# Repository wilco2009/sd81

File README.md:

# SD81 Booster — SD, sound, voice and memory interface for ZX81

An open hardware, open source project packing many features in a single interface.

## Credits

```
Hardware design & MCU firmware:  Alejandro Valero (wilco2009)
Z80 code / Modified ROM:         Pedro Gimeno (pgimeno)

Based on ZX81 ROM disassembly by Geoff Wearmouth
Preserved by Tomaž Šolc (https://www.tablix.org/~avian/spectrum/rom/)
```

## Features

- Load and save programs from/to a FAT32 microSD card in `.P` format, supporting common file and directory operations: list directory, copy/move/rename/delete files, change/create/remove directories.
- Up to 512 KB RAM, using a memory mapper in 8 KB blocks. There's also a simplified mode that allows up to 256 KB RAM, needing very simple paging code.
- The selected mapper page for any given block can be read back.
- Up to 128 user-defined characters. Compatible with the QuickSilva character definition mode — no longer restricted to the ROM's 64 characters and their inverses.
- AY-3-8910/12 sound chip emulation with `PLAY` command.
- AY VGM player, plays in background (does not support VGMs containing other chips than the AY).
- AY sound effects in background, via a programmable virtual machine (PEG).
- Speech synthesis based on the SP0256 chip (General Instrument), the same synthesiser used by the Currah MicroSpeech (ZX Spectrum) and The Voice (Videopac G7000/Odyssey 2). The `LOAD *SAY` command accepts English text directly.
- WAV audio file playback (uncompressed PCM).
- RGB colour video output, compatible with the Chroma81 interface standard.
- Real-time clock (RTC) with CR2032 backup battery.
- Programmable DB9 joystick port.
- Possibility to run code in the region between 32K and 48K (MC45 mode — see below).
- Minimal changes to the standard ROM. In particular, the ZX Printer and tape routines are preserved intact.

### What it doesn't do

- File names are restricted to characters supported by the ZX81 keyboard. The permitted characters for filenames are `A`–`Z`, `0`–`9`, `.`, `,`, `;`, `$`, `(`, `)`, `=`, `+`, `-`. The `/` character is the directory separator. Letters are treated as upper case when saving.
- AY sound chip emulation is not cycle-accurate.
- AY sound chip register access is not compatible with other interfaces.
- The memory mapping I/O port and layout are not compatible with other interfaces.
- There are no new BASIC keywords; most new functions are implemented through extensions to the `LOAD` and `SAVE` commands.

### Possible compatibility issues

- The SD81 Booster incorporates the functionality of the Chroma81 (RGB colour video) and QuickSilva (128 user-defined characters) interfaces. It is not designed to be used simultaneously with those physical interfaces connected at the same time.
- The memory area between 8 KB and 16 KB is no longer a mirror of the area between 0 and 8 KB.
- The same area is now read/write rather than read-only. If a program writes to used areas within that space, the expanded commands may crash and a hardware reset will be necessary.
- The ROM changes 8 bytes with respect to the original. Programs that depend on those specific bytes may fail (considered highly unlikely in practice).
- The memory mapper I/O port may clash with that of other interfaces.
- The general command interface I/O ports might clash with those of other interfaces.
- The USB-C port uses a CH340G chip for serial console output (115200-8N1). In Spectrum mode, port FBh is used, which is incompatible with the ZX Printer.

## MC45

MC45 (Machine Code in blocks 4 and 5) is a mode that allows any Z80 instruction — not just those with opcodes in the ranges 40h–7Fh and C0h–FFh — to run in the address range 8000h–BFFFh. The drawback is that the display file can no longer be in that area, so BASIC programs larger than 16 KB cannot be loaded or written while this mode is active.

The interface already includes a 33Ω protective resistor on the M1 line internally. No modification to the ZX81 is required. There is no jumper to disable this feature on the current hardware version.

> **Note:** Some older documentation refers to a 680Ω resistor — that value applies to an alternative ZX81 hardware modification, not to the SD81 Booster itself.

## Getting started

The **SYS** folder must be present in the root of the microSD card — without it the interface will not start. It contains the ROM files required for operation.

See [MANUAL/ES/SD81_Manual_ES.md](MANUAL/ES/SD81_Manual_ES.md) for the full user manual in Spanish.

For the technical reference and MCU command descriptions, see the [DOC folder](DOC/).

## Firmware update

**Normal update (via SD bootloader):**
1. Copy the firmware `.bin` file (renamed as `firmware.bin`) to the root of the SD card.
2. Power on the ZX81. The bootloader detects the file, flashes it at `0x0800C000`, deletes it, and boots the application.

**Emergency recovery (via USB, for advanced users):**
1. Open the interface case and bridge the two upper pins of jumper **JP7** (on the component side, next to the USB-C port).
2. Connect the USB-C cable to a PC.
3. Use **STM32CubeProgrammer** to flash:
   - Bootloader at `0x08000000`
   - Application at `0x0800C000`

See [FIRMWARE/README_update.md](FIRMWARE/README_update.md) for detailed instructions.

## Building the ZX81 ROM

The ROM listing used here is the disassembly work of [Geoff Wearmouth](http://web.archive.org/web/20150815035607/http://www.wearmouth.demon.co.uk/zx81.htm), preserved by [Tomaž Šolc](https://www.tablix.org/~avian/spectrum/rom/).

The ROM can be built using [GNU binutils for Z80](https://github.com/atsidaev/binutils-z80), [Pasmo](https://pasmo.speccy.org/) or [MDL](https://github.com/santiontanon/mdlz80optimizer).

To build with GNU binutils:

    z80-unknown-coff-as sdmodrom.asm -o sdmodrom.o
    z80-unknown-coff-ld -Ttext 0 sdmodrom.o -o sdmodrom.bin

To build with Pasmo:

    pasmo sdmodrom.asm sdmodrom.bin

To build with MDL (dialects `pasmo` or `macro80`):

    java -jar mdl.jar -dialect macro80 -bin sdmodrom.bin sdmodrom.asm

## Related projects

- [Mazogs with Chroma81 colour](https://codeberg.org/pgimeno/Mazogs) by Pedro Gimeno

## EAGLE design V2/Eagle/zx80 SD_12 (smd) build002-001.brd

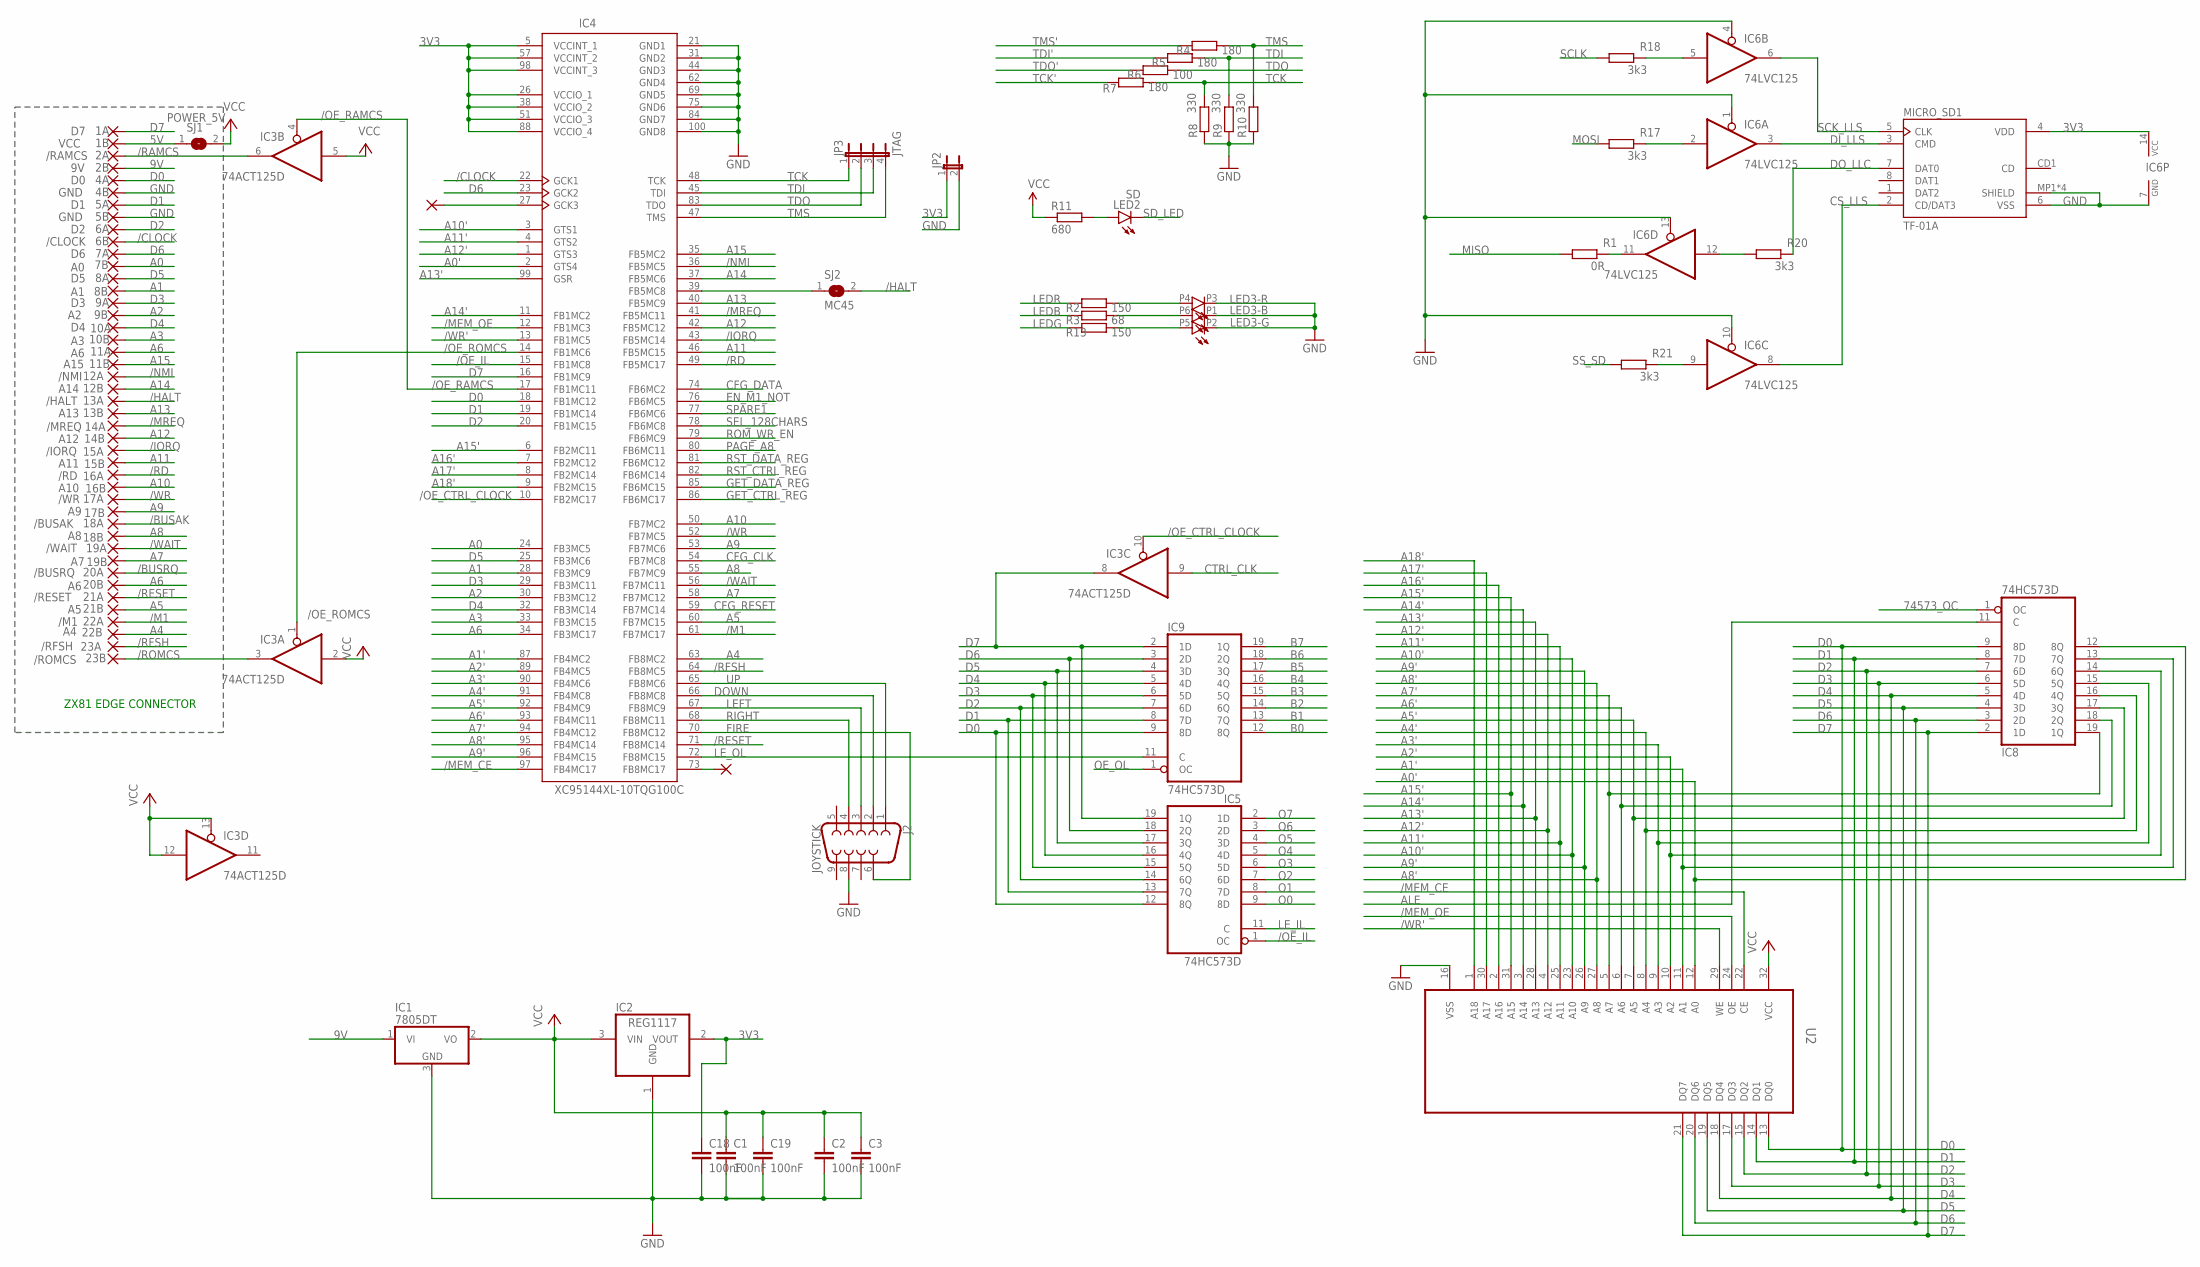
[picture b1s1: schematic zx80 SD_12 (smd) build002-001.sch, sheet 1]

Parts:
1A: D7; EDGEPIN
1B: VCC; EDGEPIN
2A: /RAMCS; EDGEPIN
2B: 9V; EDGEPIN
4A: D0; EDGEPIN
4B, 5B: GND; EDGEPIN
5A: D1; EDGEPIN
6A: D2; EDGEPIN
6B: /CLOCK; EDGEPIN
7A: D6; EDGEPIN
7B: A0; EDGEPIN
8A: D5; EDGEPIN
8B: A1; EDGEPIN
9A: D3; EDGEPIN
9B: A2; EDGEPIN
10A: D4; EDGEPIN
10B: A3; EDGEPIN
11A, 20B: A6; EDGEPIN
11B: A15; EDGEPIN
12A: /NMI; EDGEPIN
12B: A14; EDGEPIN
13A: /HALT; EDGEPIN
13B: A13; EDGEPIN
14A: /MREQ; EDGEPIN
14B: A12; EDGEPIN
15A: /IORQ; EDGEPIN
15B: A11; EDGEPIN
16A: /RD; EDGEPIN
16B: A10; EDGEPIN
17A: /WR; EDGEPIN
17B: A9; EDGEPIN
18A: /BUSAK; EDGEPIN
18B: A8; EDGEPIN
19A: /WAIT; EDGEPIN
19B: A7; EDGEPIN
20A: /BUSRQ; EDGEPIN
21A: /RESET; EDGEPIN
21B: A5; EDGEPIN
22A: /M1; EDGEPIN
22B: A4; EDGEPIN
23A: /RFSH; EDGEPIN
23B: /ROMCS; EDGEPIN
C1, C2, C3, C18, C19: 100nF; C0603
IC1: 7805DT; TO252
IC2: REG1117; SOT223
IC3: 74ACT125D; SO14
IC4: XC95144XL-10TQG100C; TQFP100
IC5, IC8, IC9: 74HC573D; SO20W
IC6: 74LVC125; SO14
J2: JOYSTICK; DB9_MALE
JP2: JP1E; JP1
JP3: JTAG; JP4
LED2: SD; CHIPLED_0603
LED3: RS-3535MWAR; 3535-PLCC6
MICRO_SD1: TF-01A
PAD1: 1,6/0,8
PAD6: P73; 1,6/0,8
R1: 0R; R0603
R2, R13: 150; R0603
R3: 68; R0603
R4, R5, R7: 180; R0603
R6: 100; R0603
R8, R9, R10: 330; R0603
R11: 680; R0603
R17, R18, R20, R21: 3k3; R0603
SJ1: POWER_5V; SJ
SJ2: MC45; SJ
U2: AS6C4008-55SINSOP5; SOP32-5

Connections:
3V3: C18.1, IC2.2 (VOUT), IC4.5 (VCCINT_1), IC4.26 (VCCIO_1), IC4.38 (VCCIO_2), IC4.51 (VCCIO_3), IC4.57 (VCCINT_2), IC4.88 (VCCIO_4), IC4.98 (VCCINT_3), IC6.14 (VCC), JP2.1, MICRO_SD1.4 (VDD); also elsewhere on the board
5V: 1B.1, SJ1.1
9V: 2B.1, IC1.1 (VI)
74573_OC: IC8.1 (OC); also elsewhere on the board
/BUSAK: 18A.1
/BUSRQ: 20A.1
/CLOCK: 6B.1, IC4.22 (GCK1)
/HALT: 13A.1, SJ2.2
/IORQ: 15A.1, IC4.43 (FB5MC14)
/M1: 22A.1, IC4.61 (FB7MC17)
/MEM_CE: IC4.97 (FB4MC17), U2.22 (CE); also elsewhere on the board
/MEM_OE: IC4.12 (FB1MC3), U2.24 (OE); also elsewhere on the board
/MREQ: 14A.1, IC4.41 (FB5MC11)
/NMI: 12A.1, IC4.36 (FB5MC5)
/OE_CTRL_CLOCK: IC3.10 (OE), IC4.10 (FB2MC17)
/OE_IL: IC4.15 (FB1MC8), IC5.1 (OC)
/OE_RAMCS: IC3.4 (OE), IC4.17 (FB1MC11)
/OE_ROMCS: IC3.1 (OE), IC4.14 (FB1MC6)
/RAMCS: 2A.1, IC3.6 (O)
/RD: 16A.1, IC4.49 (FB5MC17)
/RESET: 21A.1, IC4.71 (FB8MC14); also elsewhere on the board
/RFSH: 23A.1, IC4.64 (FB8MC5)
/ROMCS: 23B.1, IC3.3 (O)
/WAIT: 19A.1, IC4.56 (FB7MC11); also elsewhere on the board
/WR: 17A.1, IC4.52 (FB7MC5)
/WR': IC4.13 (FB1MC5), U2.29 (WE); also elsewhere on the board
A0: 7B.1, IC4.24 (FB3MC5)
A0': IC4.2 (GTS4), IC8.12 (8Q), U2.12 (A0)
A1: 8B.1, IC4.28 (FB3MC9)
A1': IC4.87 (FB4MC2), IC8.13 (7Q), U2.11 (A1)
A2: 9B.1, IC4.30 (FB3MC12)
A2': IC4.89 (FB4MC5), IC8.14 (6Q), U2.10 (A2)
A3: 10B.1, IC4.33 (FB3MC15)
A3': IC4.90 (FB4MC6), IC8.15 (5Q), U2.9 (A3)
A4: 22B.1, IC4.63 (FB8MC2)
A4': IC4.91 (FB4MC8), IC8.16 (4Q), U2.8 (A4)
A5: 21B.1, IC4.60 (FB7MC15)
A5': IC4.92 (FB4MC9), IC8.17 (3Q), U2.7 (A5)
A6: 11A.1, 20B.1, IC4.34 (FB3MC17)
A6': IC4.93 (FB4MC11), IC8.18 (2Q), U2.6 (A6)
A7: 19B.1, IC4.58 (FB7MC12)
A7': IC4.94 (FB4MC12), IC8.19 (1Q), U2.5 (A7)
A8: 18B.1, IC4.55 (FB7MC9)
A8': IC4.95 (FB4MC14), U2.27 (A8); also elsewhere on the board
A9: 17B.1, IC4.53 (FB7MC6)
A9': IC4.96 (FB4MC15), U2.26 (A9); also elsewhere on the board
A10: 16B.1, IC4.50 (FB7MC2)
A10': IC4.3 (GTS1), U2.23 (A10); also elsewhere on the board
A11: 15B.1, IC4.46 (FB5MC15)
A11': IC4.4 (GTS2), U2.25 (A11); also elsewhere on the board
A12: 14B.1, IC4.42 (FB5MC12)
A12': IC4.1 (GTS3), U2.4 (A12); also elsewhere on the board
A13: 13B.1, IC4.40 (FB5MC9)
A13': IC4.99 (GSR), U2.28 (A13); also elsewhere on the board
A14: 12B.1, IC4.37 (FB5MC6)
A14': IC4.11 (FB1MC2), U2.3 (A14); also elsewhere on the board
A15: 11B.1, IC4.35 (FB5MC2)
A15': IC4.6 (FB2MC11), U2.31 (A15); also elsewhere on the board
A16': IC4.7 (FB2MC12), U2.2 (A16); also elsewhere on the board
A17': IC4.8 (FB2MC14), U2.30 (A17); also elsewhere on the board
A18': IC4.9 (FB2MC15), U2.1 (A18); also elsewhere on the board
ALE: IC8.11 (C); also elsewhere on the board
B0: IC9.12 (8Q); also elsewhere on the board
B1: IC9.13 (7Q); also elsewhere on the board
B2: IC9.14 (6Q); also elsewhere on the board
B3: IC9.15 (5Q); also elsewhere on the board
B4: IC9.16 (4Q); also elsewhere on the board
B5: IC9.17 (3Q); also elsewhere on the board
B6: IC9.18 (2Q); also elsewhere on the board
B7: IC9.19 (1Q); also elsewhere on the board
CFG_CLK: IC4.54 (FB7MC8); also elsewhere on the board
CFG_DATA: IC4.74 (FB6MC2); also elsewhere on the board
CFG_RESET: IC4.59 (FB7MC14); also elsewhere on the board
CS_LLS: IC6.8 (O), MICRO_SD1.2 (CD/DAT3)
CTRL_CLK: IC3.9 (I); also elsewhere on the board
D0: 4A.1, IC4.18 (FB1MC12), IC5.12 (8Q), IC8.9 (8D), IC9.9 (8D), U2.13 (DQ0); also elsewhere on the board
D1: 5A.1, IC4.19 (FB1MC14), IC5.13 (7Q), IC8.8 (7D), IC9.8 (7D), U2.14 (DQ1); also elsewhere on the board
D2: 6A.1, IC4.20 (FB1MC15), IC5.14 (6Q), IC8.7 (6D), IC9.7 (6D), U2.15 (DQ2); also elsewhere on the board
D3: 9A.1, IC4.29 (FB3MC11), IC5.15 (5Q), IC8.6 (5D), IC9.6 (5D), U2.17 (DQ3); also elsewhere on the board
D4: 10A.1, IC4.32 (FB3MC14), IC5.16 (4Q), IC8.5 (4D), IC9.5 (4D), U2.18 (DQ4); also elsewhere on the board
D5: 8A.1, IC4.25 (FB3MC6), IC5.17 (3Q), IC8.4 (3D), IC9.4 (3D), U2.19 (DQ5); also elsewhere on the board
D6: 7A.1, IC4.23 (GCK2), IC5.18 (2Q), IC8.3 (2D), IC9.3 (2D), U2.20 (DQ6); also elsewhere on the board
D7: 1A.1, IC3.8 (O), IC4.16 (FB1MC9), IC5.19 (1Q), IC8.2 (1D), IC9.2 (1D), U2.21 (DQ7); also elsewhere on the board
DI_LLS: IC6.3 (O), MICRO_SD1.3 (CMD)
DOWN: IC4.66 (FB8MC8), J2.2
DO_LLC: IC6.12 (I), R20.1
EN_M1_NOT: IC4.76 (FB6MC5); also elsewhere on the board
FIRE: IC4.70 (FB8MC12), J2.6
GET_CTRL_REG: IC4.86 (FB6MC17); also elsewhere on the board
GET_DATA_REG: IC4.85 (FB6MC15); also elsewhere on the board
GND: 4B.1, 5B.1, C1.2, C2.2, C3.2, C18.2, C19.2, IC1.3 (GND), IC2.1 (GND), IC3.7 (GND), IC4.21 (GND1), IC4.31 (GND2), IC4.44 (GND3), IC4.62 (GND4), IC4.69 (GND5), IC4.75 (GND6), IC4.84 (GND7), IC4.100 (GND8), IC5.10 (GND), IC6.1 (OE), IC6.4 (OE), IC6.7 (GND), IC6.10 (OE), IC6.13 (OE), IC8.10 (GND), IC9.10 (GND), J2.8, JP2.2, LED3.P1 (C), LED3.P2 (C), LED3.P3 (C), MICRO_SD1.6 (VSS), MICRO_SD1.MP1 (SHIELD), MICRO_SD1.MP2 (SHIELD), MICRO_SD1.MP3 (SHIELD), MICRO_SD1.MP4 (SHIELD), R8.1, R9.1, R10.1, U2.16 (VSS); also elsewhere on the board
LEDB: R3.1; also elsewhere on the board
LEDG: R13.1; also elsewhere on the board
LEDR: R2.1; also elsewhere on the board
LEFT: IC4.67 (FB8MC9), J2.3
LE_IL: IC5.11 (C); also elsewhere on the board
LE_OL: IC4.72 (FB8MC15), IC9.11 (C)
MISO: R1.1; also elsewhere on the board
MOSI: R17.1; also elsewhere on the board
unnamed: IC6.2 (I), R17.2
unnamed: IC6.11 (O), R1.2
unnamed: IC6.5 (I), R18.2
unnamed: MICRO_SD1.7 (DAT0), R20.2
unnamed: IC6.9 (I), R21.2
unnamed: LED2.A, R11.2
unnamed: IC4.73 (FB8MC17), PAD6.1
unnamed: IC4.27 (GCK3), PAD1.1
unnamed: LED3.P4 (A), R2.2
unnamed: LED3.P6 (A), R3.2
unnamed: LED3.P5 (A), R13.2
unnamed: IC4.39 (FB5MC8), SJ2.1
O0: IC5.9 (8D); also elsewhere on the board
O1: IC5.8 (7D); also elsewhere on the board
O2: IC5.7 (6D); also elsewhere on the board
O3: IC5.6 (5D); also elsewhere on the board
O4: IC5.5 (4D); also elsewhere on the board
O5: IC5.4 (3D); also elsewhere on the board
O6: IC5.3 (2D); also elsewhere on the board
O7: IC5.2 (1D); also elsewhere on the board
OE_OL: IC9.1 (OC); also elsewhere on the board
PAGE_A8: IC4.80 (FB6MC11); also elsewhere on the board
RIGHT: IC4.68 (FB8MC11), J2.4
ROM_WR_EN: IC4.79 (FB6MC9); also elsewhere on the board
RST_CTRL_REG: IC4.82 (FB6MC14); also elsewhere on the board
RST_DATA_REG: IC4.81 (FB6MC12); also elsewhere on the board
SCK_LLS: IC6.6 (O), MICRO_SD1.5 (CLK)
SCLK: R18.1; also elsewhere on the board
SD_LED: LED2.C; also elsewhere on the board
SEL_128CHARS: IC4.78 (FB6MC8); also elsewhere on the board
SPARE1: IC4.77 (FB6MC6); also elsewhere on the board
SS_SD: R21.1; also elsewhere on the board
TCK: IC4.48 (TCK), JP3.1, R7.2, R8.2
TCK': R7.1; also elsewhere on the board
TDI: IC4.45 (TDI), JP3.3, R5.2, R9.2
TDI': R5.1; also elsewhere on the board
TDO: IC4.83 (TDO), JP3.2, R6.2
TDO': R6.1; also elsewhere on the board
TMS: IC4.47 (TMS), JP3.4, R4.2, R10.2
TMS': R4.1; also elsewhere on the board
UP: IC4.65 (FB8MC6), J2.1
VCC: C1.1, C2.1, C3.1, C19.1, IC1.2 (VO), IC2.3 (VIN), IC3.2 (I), IC3.5 (I), IC3.12 (I), IC3.13 (OE), IC3.14 (VCC), IC5.20 (VCC), IC8.20 (VCC), IC9.20 (VCC), R11.1, SJ1.2, U2.32 (VCC); also elsewhere on the board

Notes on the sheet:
ZX81 EDGE CONNECTOR

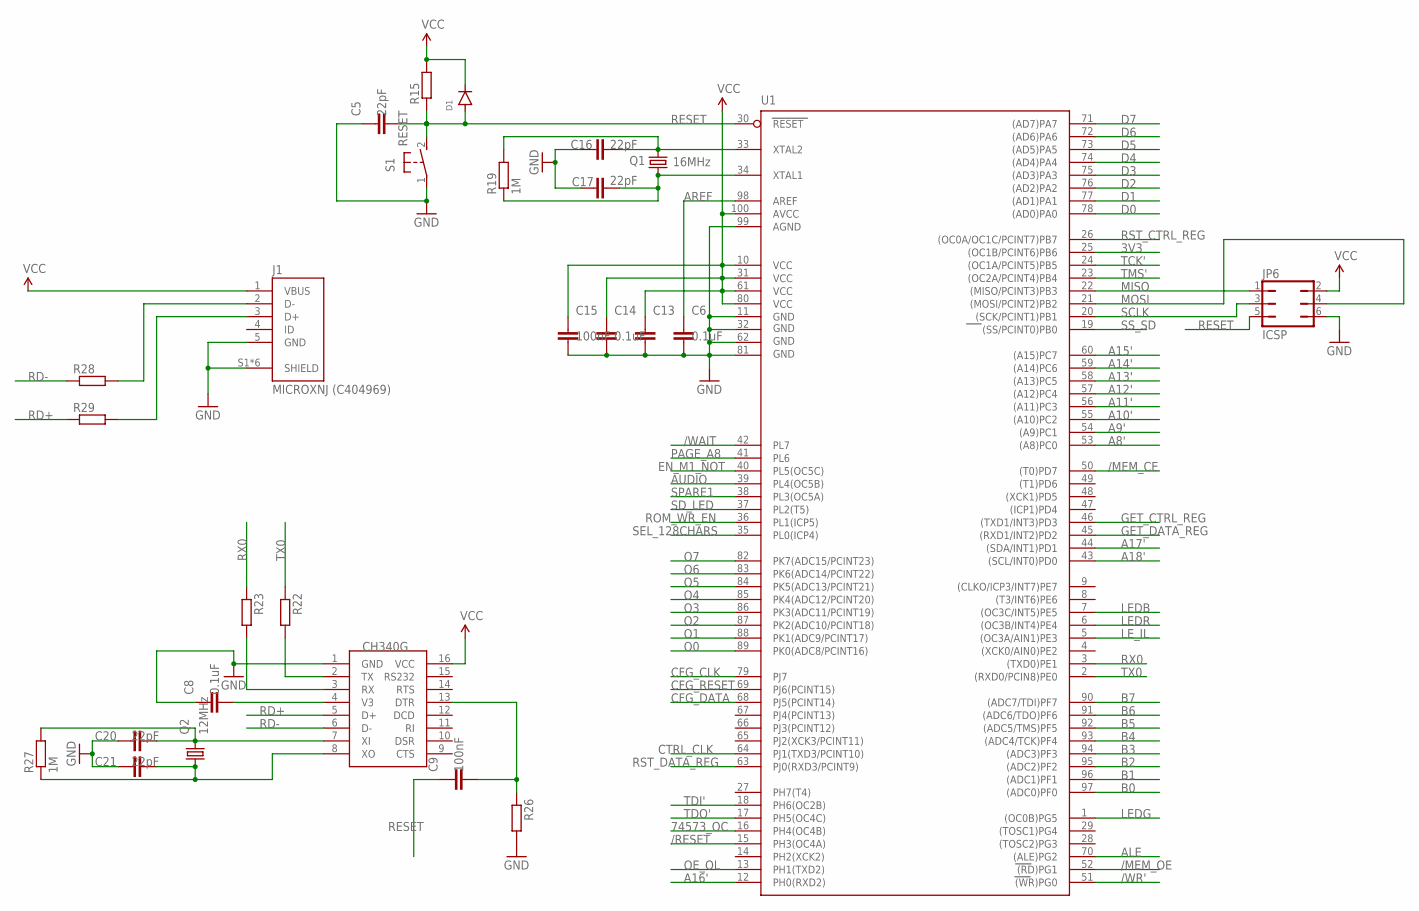
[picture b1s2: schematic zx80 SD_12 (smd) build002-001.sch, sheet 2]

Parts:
C5, C16, C17, C20, C21: 22pF; C0603
C6, C8, C13, C14: 0.1uF; C0603
C9, C15: 100nF; C0603
D1: DIODE-SOD123; SOD123
IC7: CH340G; SOIC16
J1: MICROXNJ (C404969); SHOUHAN_MICROXNJ
JP6: ICSP; JP3Q
Q1: 16MHz; 3.2X2.5_KX-7
Q2: 12MHz; 3.2X2.5_KX-7
R15: R0603
R19, R27: 1M; R0603
R22, R23, R26: 1K; R0603
R28, R29: 22R; R0603
S1: RESET; B3F-31XX
U1: ATMEGA2560AU; TQFP100

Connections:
3V3: U1.25 ((OC1B/PCINT6)PB6); also elsewhere on the board
74573_OC: U1.16 (PH4(OC4B)); also elsewhere on the board
/MEM_CE: U1.50 ((T0)PD7); also elsewhere on the board
/MEM_OE: U1.52 ((RD)PG1); also elsewhere on the board
/RESET: U1.15 (PH3(OC4A)); also elsewhere on the board
/WAIT: U1.42 (PL7); also elsewhere on the board
/WR': U1.51 ((WR)PG0); also elsewhere on the board
A8': U1.53 ((A8)PC0); also elsewhere on the board
A9': U1.54 ((A9)PC1); also elsewhere on the board
A10': U1.55 ((A10)PC2); also elsewhere on the board
A11': U1.56 ((A11)PC3); also elsewhere on the board
A12': U1.57 ((A12)PC4); also elsewhere on the board
A13': U1.58 ((A13)PC5); also elsewhere on the board
A14': U1.59 ((A14)PC6); also elsewhere on the board
A15': U1.60 ((A15)PC7); also elsewhere on the board
A16': U1.12 (PH0(RXD2)); also elsewhere on the board
A17': U1.44 ((SDA/INT1)PD1); also elsewhere on the board
A18': U1.43 ((SCL/INT0)PD0); also elsewhere on the board
ALE: U1.70 ((ALE)PG2); also elsewhere on the board
AREF: C6.1, U1.98 (AREF)
AUDIO: U1.39 (PL4(OC5B))
B0: U1.97 ((ADC0)PF0); also elsewhere on the board
B1: U1.96 ((ADC1)PF1); also elsewhere on the board
B2: U1.95 ((ADC2)PF2); also elsewhere on the board
B3: U1.94 ((ADC3)PF3); also elsewhere on the board
B4: U1.93 ((ADC4/TCK)PF4); also elsewhere on the board
B5: U1.92 ((ADC5/TMS)PF5); also elsewhere on the board
B6: U1.91 ((ADC6/TDO)PF6); also elsewhere on the board
B7: U1.90 ((ADC7/TDI)PF7); also elsewhere on the board
CFG_CLK: U1.79 (PJ7); also elsewhere on the board
CFG_DATA: U1.68 (PJ5(PCINT14)); also elsewhere on the board
CFG_RESET: U1.69 (PJ6(PCINT15)); also elsewhere on the board
CTRL_CLK: U1.64 (PJ1(TXD3/PCINT10)); also elsewhere on the board
D0: U1.78 ((AD0)PA0); also elsewhere on the board
D1: U1.77 ((AD1)PA1); also elsewhere on the board
D2: U1.76 ((AD2)PA2); also elsewhere on the board
D3: U1.75 ((AD3)PA3); also elsewhere on the board
D4: U1.74 ((AD4)PA4); also elsewhere on the board
D5: U1.73 ((AD5)PA5); also elsewhere on the board
D6: U1.72 ((AD6)PA6); also elsewhere on the board
D7: U1.71 ((AD7)PA7); also elsewhere on the board
EN_M1_NOT: U1.40 (PL5(OC5C)); also elsewhere on the board
GET_CTRL_REG: U1.46 ((TXD1/INT3)PD3); also elsewhere on the board
GET_DATA_REG: U1.45 ((RXD1/INT2)PD2); also elsewhere on the board
GND: C5.1, C6.2, C8.1, C13.2, C14.2, C15.2, C16.1, C17.1, C20.1, C21.1, IC7.1 (GND), J1.5 (GND), J1.S1 (SHIELD), J1.S2 (SHIELD), J1.S3 (SHIELD), J1.S4 (SHIELD), J1.S5 (SHIELD), J1.S6 (SHIELD), JP6.6, R26.2, S1.1, U1.11 (GND), U1.32 (GND1), U1.62 (GND2), U1.81 (GND3), U1.99 (AGND); also elsewhere on the board
LEDB: U1.7 ((OC3C/INT5)PE5); also elsewhere on the board
LEDG: U1.1 ((OC0B)PG5); also elsewhere on the board
LEDR: U1.6 ((OC3B/INT4)PE4); also elsewhere on the board
LE_IL: U1.5 ((OC3A/AIN1)PE3); also elsewhere on the board
MISO: JP6.1, U1.22 ((MISO/PCINT3)PB3); also elsewhere on the board
MOSI: JP6.4, U1.21 ((MOSI/PCINT2)PB2); also elsewhere on the board
unnamed: IC7.2 (TX), R22.2
unnamed: IC7.3 (RX), R23.2
unnamed: C8.2, IC7.4 (V3)
unnamed: C20.2, IC7.7 (XI), Q2.3 (2), R27.2
unnamed: C21.2, IC7.8 (XO), Q2.1, R27.1
unnamed: C16.2, Q1.3 (2), R19.2, U1.33 (XTAL2)
unnamed: C17.2, Q1.1, R19.1, U1.34 (XTAL1)
unnamed: C9.2, IC7.13 (DTR), R26.1
unnamed: J1.2 (D-), R28.2
unnamed: J1.3 (D+), R29.2
O0: U1.89 (PK0(ADC8/PCINT16)); also elsewhere on the board
O1: U1.88 (PK1(ADC9/PCINT17)); also elsewhere on the board
O2: U1.87 (PK2(ADC10/PCINT18)); also elsewhere on the board
O3: U1.86 (PK3(ADC11/PCINT19)); also elsewhere on the board
O4: U1.85 (PK4(ADC12/PCINT20)); also elsewhere on the board
O5: U1.84 (PK5(ADC13/PCINT21)); also elsewhere on the board
O6: U1.83 (PK6(ADC14/PCINT22)); also elsewhere on the board
O7: U1.82 (PK7(ADC15/PCINT23)); also elsewhere on the board
OE_OL: U1.13 (PH1(TXD2)); also elsewhere on the board
PAGE_A8: U1.41 (PL6); also elsewhere on the board
RD+: IC7.5 (D+), R29.1
RD-: IC7.6 (D-), R28.1
RESET: C5.2, C9.1, D1.A, JP6.5, R15.1, S1.2 (S), U1.30 (RESET)
ROM_WR_EN: U1.36 (PL1(ICP5)); also elsewhere on the board
RST_CTRL_REG: U1.26 ((OC0A/OC1C/PCINT7)PB7); also elsewhere on the board
RST_DATA_REG: U1.63 (PJ0(RXD3/PCINT9)); also elsewhere on the board
RX0: R23.1, U1.3 ((TXD0)PE1)
SCLK: JP6.3, U1.20 ((SCK/PCINT1)PB1); also elsewhere on the board
SD_LED: U1.37 (PL2(T5)); also elsewhere on the board
SEL_128CHARS: U1.35 (PL0(ICP4)); also elsewhere on the board
SPARE1: U1.38 (PL3(OC5A)); also elsewhere on the board
SS_SD: U1.19 ((SS/PCINT0)PB0); also elsewhere on the board
TCK': U1.24 ((OC1A/PCINT5)PB5); also elsewhere on the board
TDI': U1.18 (PH6(OC2B)); also elsewhere on the board
TDO': U1.17 (PH5(OC4C)); also elsewhere on the board
TMS': U1.23 ((OC2A/PCINT4)PB4); also elsewhere on the board
TX0: R22.1, U1.2 ((RXD0/PCIN8)PE0)
VCC: C13.1, C14.1, C15.1, D1.C, IC7.16 (VCC), J1.1 (VBUS), JP6.2, R15.2, U1.10 (VCC), U1.31 (VCC1), U1.61 (VCC2), U1.80 (VCC3), U1.100 (AVCC); also elsewhere on the board

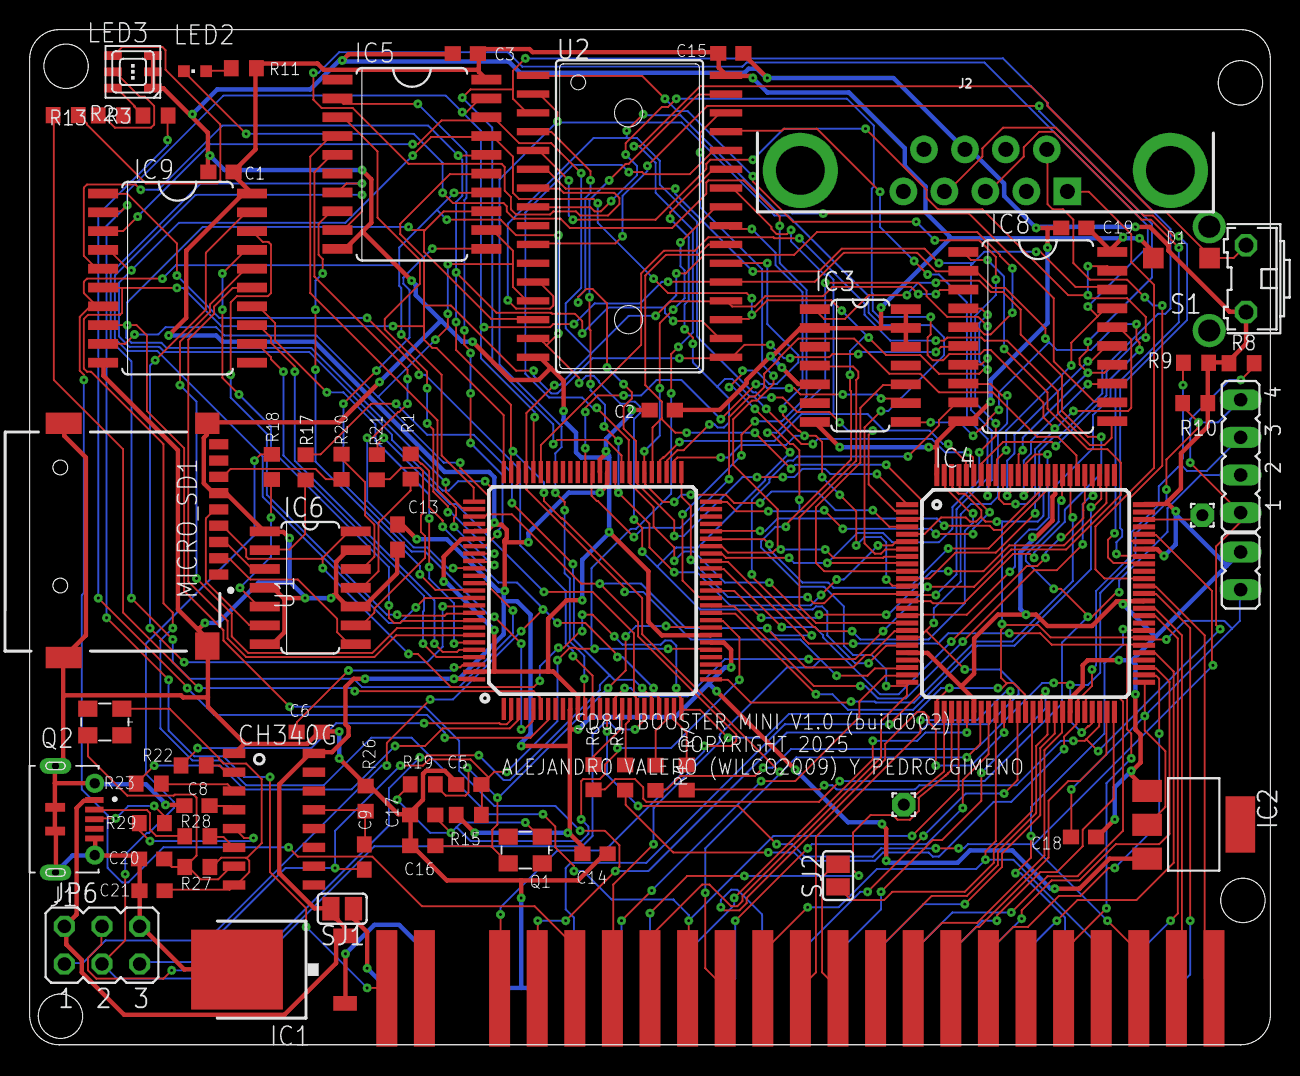
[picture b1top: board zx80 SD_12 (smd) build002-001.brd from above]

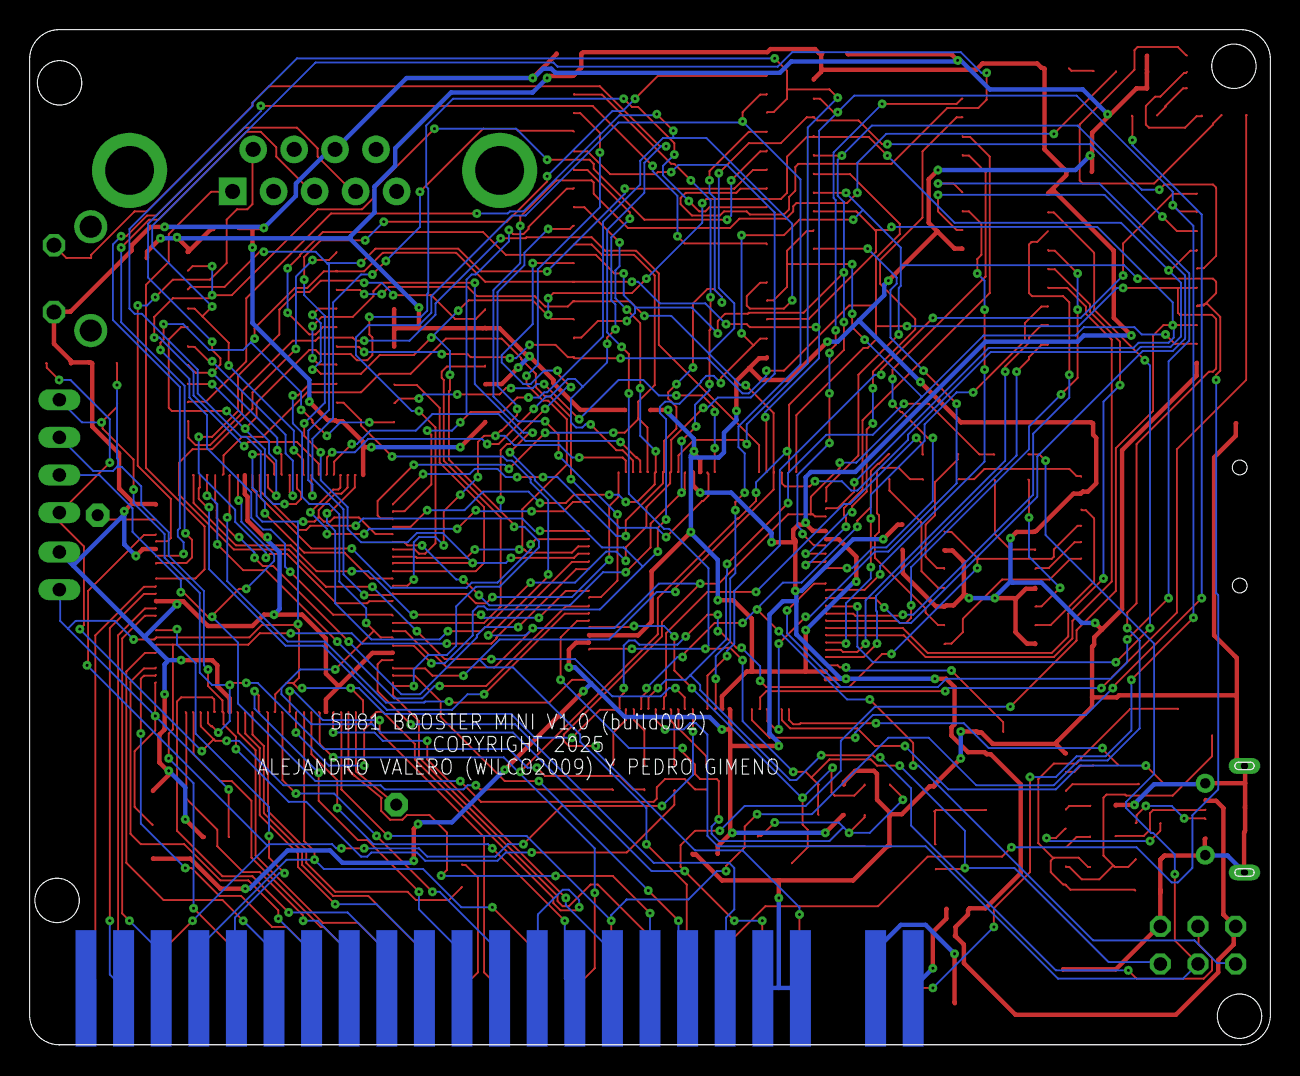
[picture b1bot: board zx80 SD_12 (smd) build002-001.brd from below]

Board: 2 copper layers, 83.8 x 68.6 mm, 111 parts (22 on the bottom side), 155 nets.

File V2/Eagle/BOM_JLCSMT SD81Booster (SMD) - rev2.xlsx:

Comment | Designator | Footprint | JLCPCB Part #（optional）
100nF | C1 | C0603 | C14663
100nF | C2 | C0603 | C14663
100nF | C3 | C0603 | C14663
22pF | C5 | C0603 | C1653
100nF | C6 | C0603 | C14663
100nF | C8 | C0603 | C14663
100nF | C9 | C0603 | C14663
100nF | C13 | C0603 | C14663
100nF | C14 | C0603 | C14663
100nF | C15 | C0603 | C14663
22pF | C16 | C0603 | C1653
22pF | C17 | C0603 | C1653
100nF | C18 | C0603 | C14663
100nF | C19 | C0603 | C14663
22pF | C20 | C0603 | C91701
22pF | C21 | C0603 | C91701
1n4148 | D1 | SOD123 | C81598
7805 | IC1 | TO252
REG1117 | IC2 | SOT223 | C5400
74ACT125D | IC3 | SO14 | C113254
XC95144XL-10TQG100C | IC4 | TQFP100 | C45126
74HC573D | IC5 | SO20W | C5122488
74LVC125 | IC6 | SO14 | C7661
CH340G | IC7 | SOIC16 | C14267
74HC573D | IC8 | SO20W | C5122488
74HC573D | IC9 | SO20W | C5122488
MICROXNJ (C404969) | J1 | SHOUHAN_MICROXNJ | C404969
DB9 | J2
ICSP | JP6 | JP3Q | C124384
KT-0603B | LED2 | D603 | C7496819
RS-3535MWAR | LED3 | SMD3535 | C110402
TF-01A | MICRO_SD1 | TF-01A | C2889258
16MHz | Q1 | 3,2X2,5_KX-7 | C280836
12MHz | Q2 | 3,2X2,5_KX-7 | C93234
0R | R1 | R0603 | C21189
150 | R2 | R0603 | C22808
68 | R3 | R0603 | C27592
180 | R4 | R0603 | C22828
180 | R5 | R0603 | C22828
100 | R6 | R0603 | C22775
180 | R7 | R0603 | C22828
330 | R8 | R0603 | C23138
330 | R9 | R0603 | C23138
330 | R10 | R0603 | C23138
680 | R11 | R0603 | C23228
150 | R13 | R0603 | C22808
10K | R15 | R0603 | C15401
3k3 | R17 | R0603 | C22978
3k3 | R18 | R0603 | C22978
1M | R19 | R0603 | C22935
3k3 | R20 | R0603 | C22978
3k3 | R21 | R0603 | C22978
1K | R22 | R0603 | C21190
1K | R23 | R0603 | C21190
1K | R26 | R0603 | C21190
1M | R27 | R0603 | C22935
22R | R28 | R0603 | C1203
22R | R29 | R0603 | C1203
RESET | S1 | B3F-31XX
ATMEGA2560AU | U1 | TQFP100 | C22460
AS6C4008-55SIN | U2 | SOIC127P1407X299-32N | C2952831

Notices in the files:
V2/Eagle/zx80 SD_12 (smd) build002-001.brd:
COPYRIGHT 2025
V2/Eagle/zx81 SD_10.brd:
COPYRIGHT 2023
parts and their libraries:
SparkFun-IC-Microcontroller: Licensing: Creative Commons ShareAlike 4.0 International - https://creativecommons.org/licenses/by-sa/4.0
crystal-geyer_V1_0: Copyright: Geyer-Electronic
